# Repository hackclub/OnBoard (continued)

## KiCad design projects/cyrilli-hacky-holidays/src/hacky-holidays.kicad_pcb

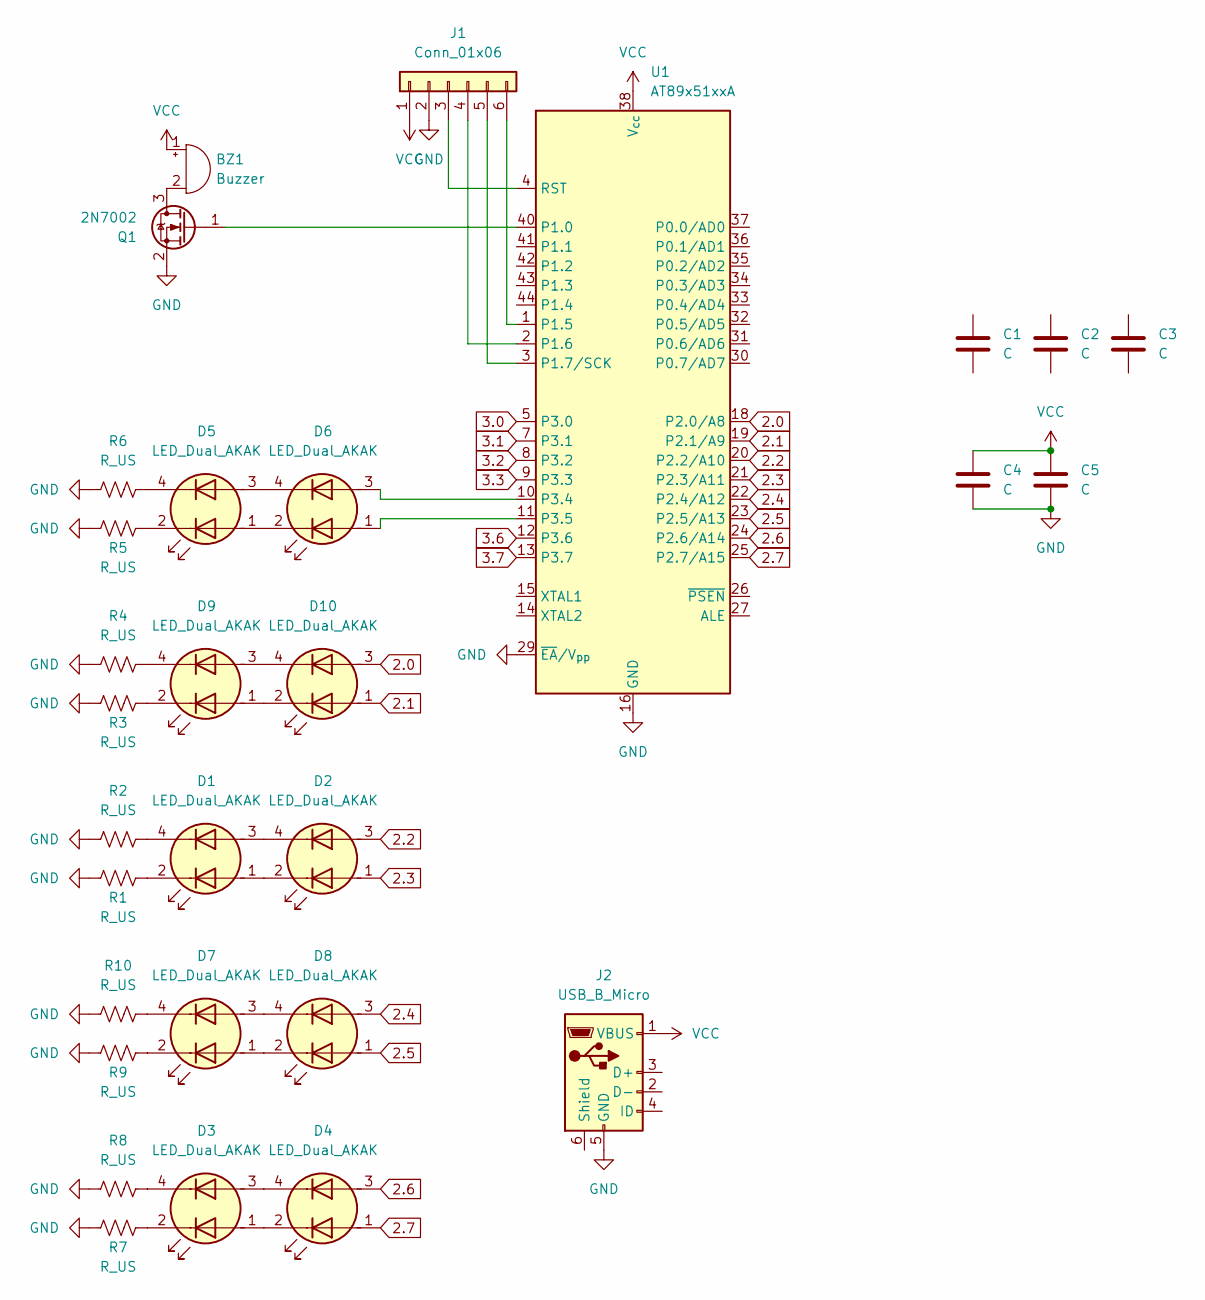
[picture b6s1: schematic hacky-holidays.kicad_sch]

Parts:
BZ1: Buzzer; BUZ-SMD_FST-9018
C1, C2, C3, C4, C5: C; C_0402_1005Metric
D1, D2, D3, D4, D5, D6, D7, D8, D9, D10: LED_Dual_AKAK; LED-ARRAY-SMD_4P-L1.6-W1.5-BR-A
J1: Conn_01x06; HDR-SMD_6P-P2.54-V-M-S4.8
J2: USB_B_Micro; MICRO-USB-SMD_USB-MR-D-023
Q1: 2N7002; SOT-23
R1, R2, R3, R4, R5, R6, R7, R8, R9, R10: R_US; R_0402_1005Metric
U1: AT89x51xxA; TQFP-44_10x10mm_P0.8mm

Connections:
2.0: D10.3 (A2), U1.18 (P2.0/A8)
2.1: D10.1 (A1), U1.19 (P2.1/A9)
2.2: D2.3 (A2), U1.20 (P2.2/A10)
2.3: D2.1 (A1), U1.21 (P2.3/A11)
2.4: D8.3 (A2), U1.22 (P2.4/A12)
2.5: D8.1 (A1), U1.23 (P2.5/A13)
2.6: D4.3 (A2), U1.24 (P2.6/A14)
2.7: D4.1 (A1), U1.25 (P2.7/A15)
3.0: U1.5 (P3.0)
3.1: U1.7 (P3.1)
3.2: U1.8 (P3.2)
3.3: U1.9 (P3.3)
3.6: U1.12 (P3.6)
3.7: U1.13 (P3.7)
GND: C4.2, C5.2, J1.2, J2.5 (GND), Q1.2 (S), R1.1, R2.1, R3.1, R4.1, R5.1, R6.1, R7.1, R8.1, R9.1, R10.1, U1.16 (GND), U1.17 (GND), U1.29 (~EA/V_{pp})
unnamed: BZ1.2 (-), Q1.3 (D)
unnamed: D1.1 (A1), D2.2 (K1)
unnamed: D1.3 (A2), D2.4 (K2)
unnamed: D1.2 (K1), R1.2
unnamed: D1.4 (K2), R2.2
unnamed: D3.1 (A1), D4.2 (K1)
unnamed: D3.3 (A2), D4.4 (K2)
unnamed: D3.2 (K1), R7.2
unnamed: D3.4 (K2), R8.2
unnamed: D5.1 (A1), D6.2 (K1)
unnamed: D5.3 (A2), D6.4 (K2)
unnamed: D5.2 (K1), R5.2
unnamed: D5.4 (K2), R6.2
unnamed: D6.1 (A1), U1.11 (P3.5)
unnamed: D6.3 (A2), U1.10 (P3.4)
unnamed: D7.1 (A1), D8.2 (K1)
unnamed: D7.3 (A2), D8.4 (K2)
unnamed: D7.2 (K1), R9.2
unnamed: D7.4 (K2), R10.2
unnamed: D9.2 (K1), R3.2
unnamed: D9.4 (K2), R4.2
unnamed: D9.1 (A1), D10.2 (K1)
unnamed: D9.3 (A2), D10.4 (K2)
unnamed: J1.3, U1.4 (RST)
unnamed: J1.4, U1.2 (P1.6)
unnamed: J1.5, U1.3 (P1.7/SCK)
unnamed: J1.6, U1.1 (P1.5)
unnamed: Q1.1 (G), U1.40 (P1.0)
VCC: BZ1.1 (+), C4.1, C5.1, J1.1, J2.1 (VBUS), U1.38 (V_{cc})

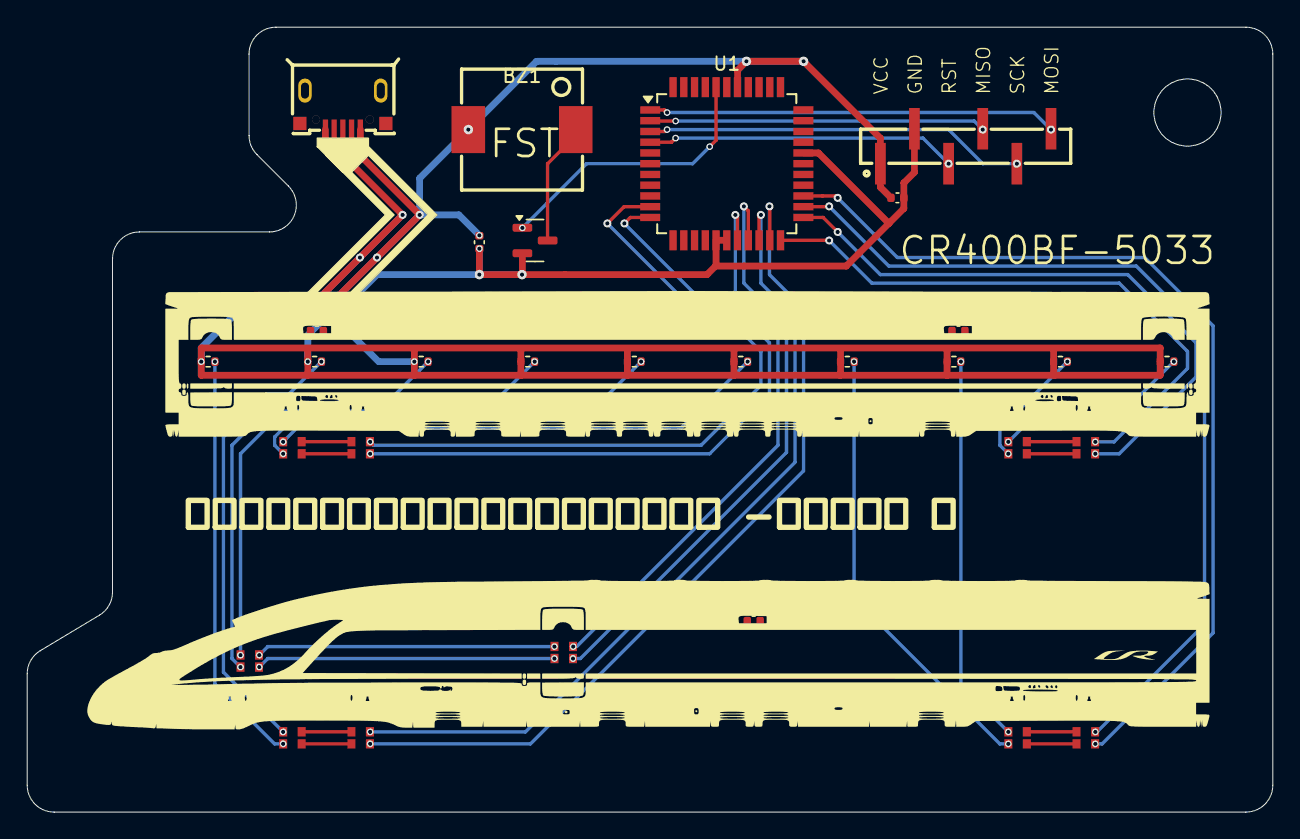
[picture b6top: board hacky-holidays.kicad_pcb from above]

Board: 2 copper layers, 92.7 x 58.4 mm, 30 parts (0 on the bottom side), 38 nets.

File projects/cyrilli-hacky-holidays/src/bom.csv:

Designator,Footprint,Quantity,Value,LCSC Part #
BZ1,BUZ-SMD_FST-9018,1,Buzzer,C391035
"C1, C2, C3, C4, C5",0402,5,C, C1525
"D1, D10, D2, D3, D4, D5, D6, D7, D8, D9",LED-ARRAY-SMD_4P-L1.6-W1.5-BR-A,10,LED_Dual_AKAK,
J1,HDR-SMD_6P-P2.54-V-M-S4.8,1,Conn_01x06,C22438430
J2,MICRO-USB-SMD_USB-MR-D-023,1,USB_B_Micro,
Q1,SOT-23,1,2N7002,
"R1, R10, R2, R3, R4, R5, R6, R7, R8, R9",0402,10,R_US,C25091
U1,TQFP-44_10x10mm_P0.8mm,1,AT89x51xxA,C618936

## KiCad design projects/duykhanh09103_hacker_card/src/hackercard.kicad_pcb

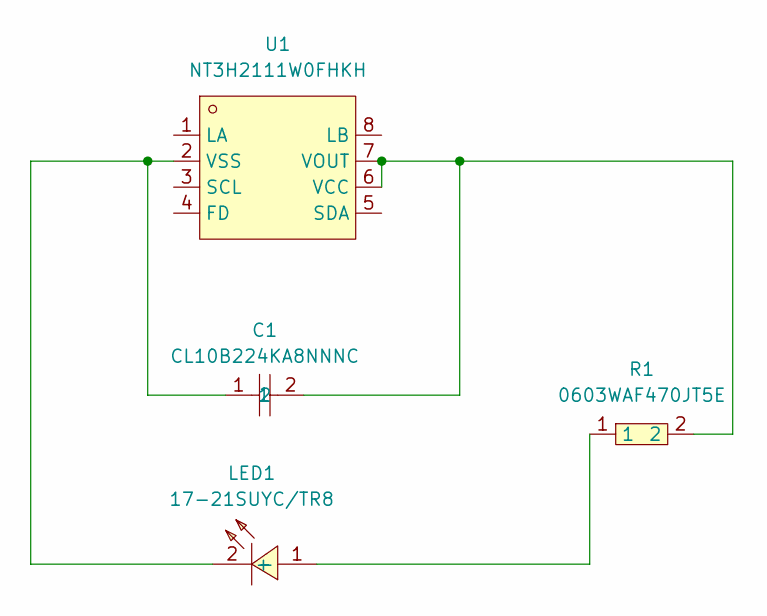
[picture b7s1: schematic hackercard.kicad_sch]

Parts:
C1: CL10B224KA8NNNC; C0603; LCSC Part C21120
LED1: 17-21SUYC/TR8; LED0805-R-RD; LCSC Part C2296
R1: 0603WAF470JT5E; R0603; LCSC Part C23182
U1: NT3H2111W0FHKH; XQFN-8_L1.6-W1.6-P0.50-BL_NT3H2111W0FHKH; LCSC Part C710403

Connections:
unnamed: LED1.1 (+), R1.1
unnamed: C1.1, LED1.2 (-), U1.2 (VSS)
unnamed: C1.2, R1.2, U1.6 (VCC), U1.7 (VOUT)

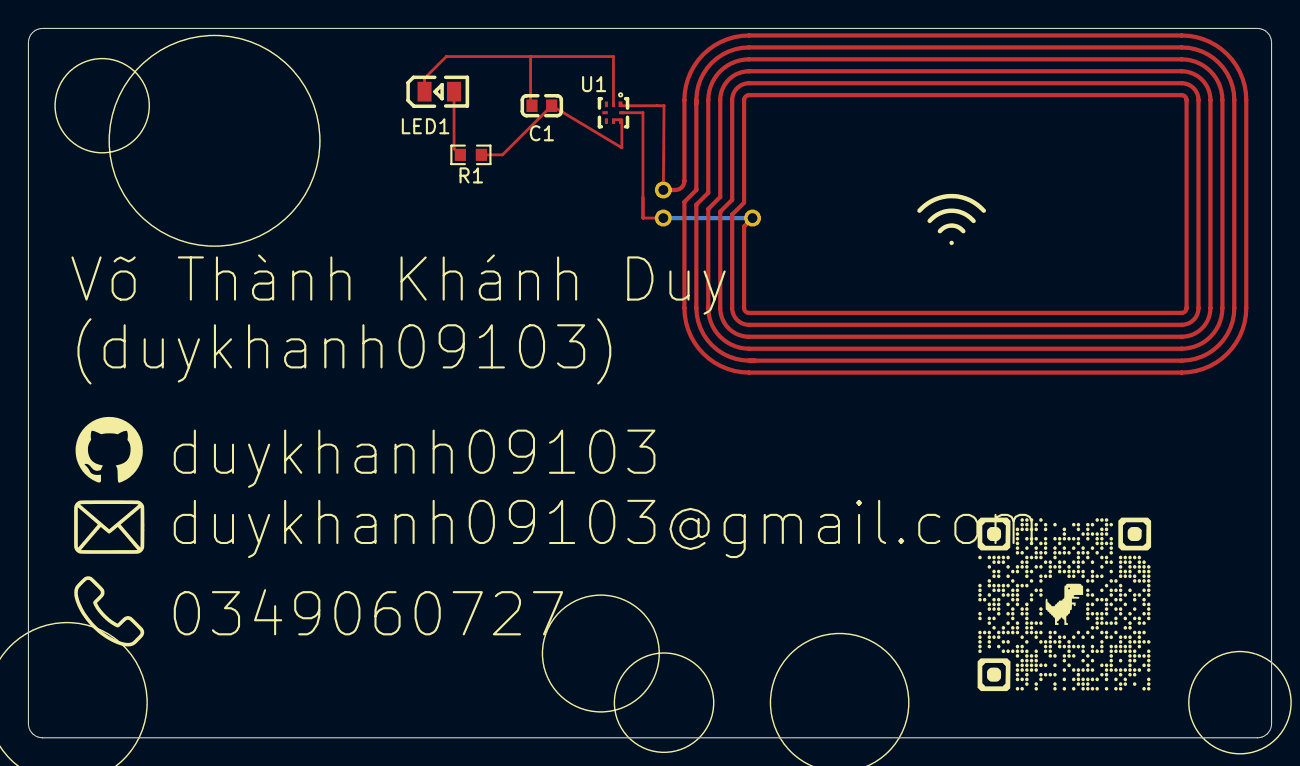
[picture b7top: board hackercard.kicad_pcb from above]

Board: 2 copper layers, 88.5 x 50.5 mm, 8 parts (0 on the bottom side), 3 nets.

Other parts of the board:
Mail: LOGO
github: LOGO
github qr code: LOGO
phone: LOGO

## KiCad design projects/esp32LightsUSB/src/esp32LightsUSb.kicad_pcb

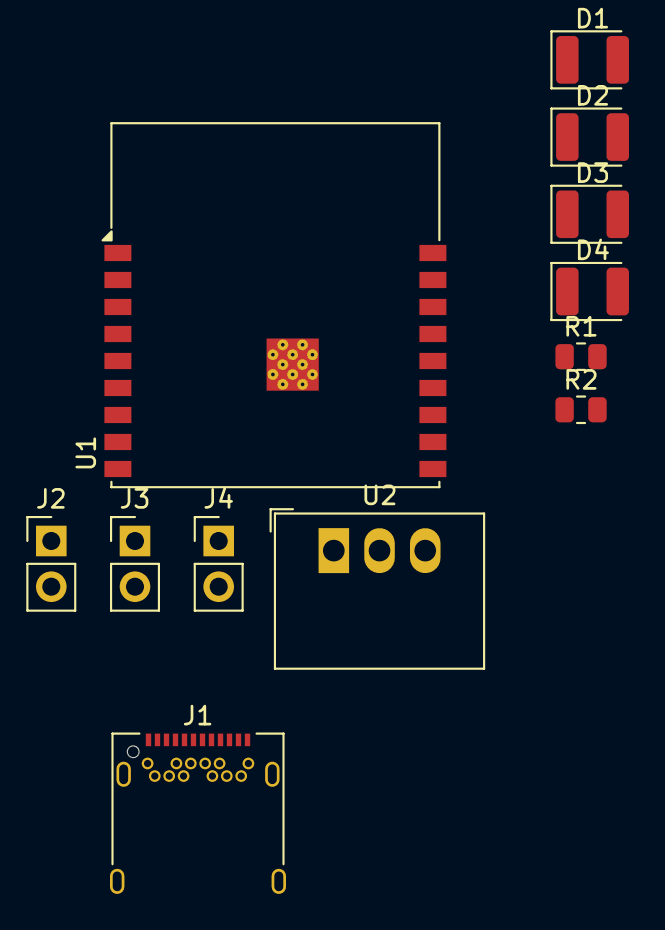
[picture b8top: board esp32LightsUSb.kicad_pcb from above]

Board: 2 copper layers, 12 parts (0 on the bottom side), 12 nets, no tracks yet.

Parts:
D1, D2, D3, D4: LED; LED_1210_3225Metric
J1: USB_C_Receptacle; USB_C_Receptacle_Amphenol_12401548E4-2A
J2, J3, J4: Conn_01x02; PinHeader_1x02_P2.54mm_Vertical
R1, R2: 5.11k; R_0805_2012Metric
U1: ESP32-C3-WROOM-02
U2: R-78B3.3-2.0; Converter_DCDC_RECOM_R-78B-2.0_THT

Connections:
GND: D1.1 (K), D2.1 (K), D3.1 (K), D4.1 (K), J1.A1 (GND), J1.A12 (GND), J1.B1 (GND), J1.B12 (GND), J1.S1 (SHIELD), J4.2, R1.1, R2.2, U1.9 (GND), U1.19 (GND), U2.2 (GND)
unnamed: D1.2 (A), U1.15 (IO3)
unnamed: D2.2 (A), U1.3 (IO4)
unnamed: D3.2 (A), U1.4 (IO5)
unnamed: D4.2 (A), U1.5 (IO6)
unnamed: J1.A5 (CC1), R2.1
unnamed: J1.B5 (CC2), R1.2
unnamed: J2.1, U1.2 (EN)
unnamed: J2.2, J4.1, U1.1 (3V3), U2.3 (OUT)
unnamed: J3.1, U1.11 (IO20/RXD)
unnamed: J3.2, U1.12 (IO21/TXD)
VBUS: J1.A4 (VBUS), J1.A9 (VBUS), J1.B4 (VBUS), J1.B9 (VBUS), U2.1 (IN)

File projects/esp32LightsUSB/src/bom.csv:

Designator,Footprint,Quantity,Value,LCSC Part #
"D1, D2, D3, D4",1210,4,LED,
J1,USB_C_Receptacle_Amphenol_12401548E4-2A,1,USB_C_Receptacle,
"J2, J3, J4",PinHeader_1x02_P2.54mm_Vertical,3,Conn_01x02,
"R1, R2",0805,2,5.11k,
U1,ESP32-C3-WROOM-02,1,ESP32-C3-WROOM-02,
U2,Converter_DCDC_RECOM_R-78B-2.0_THT,1,R-78B3.3-2.0,
